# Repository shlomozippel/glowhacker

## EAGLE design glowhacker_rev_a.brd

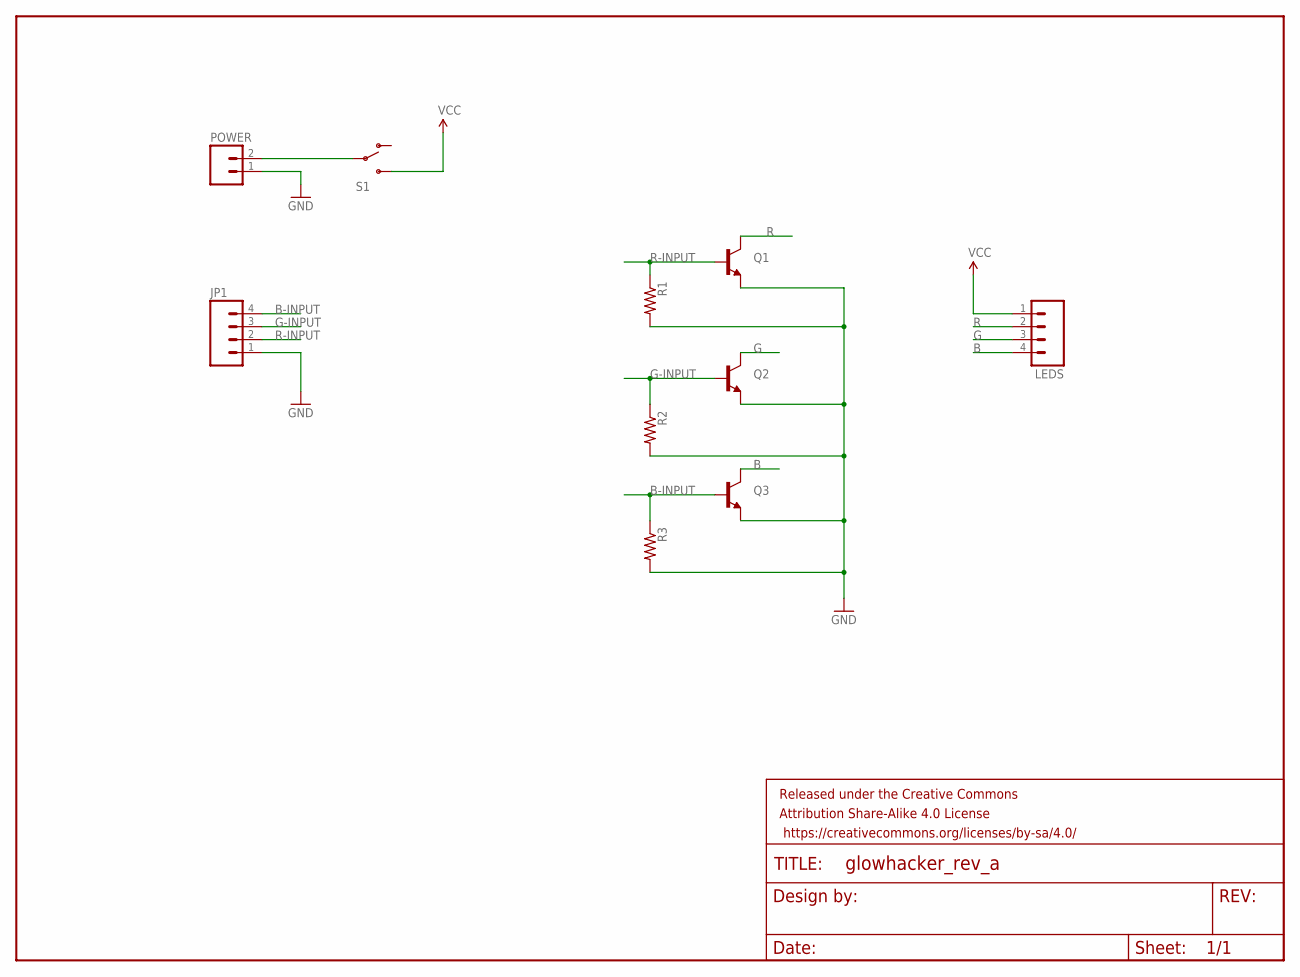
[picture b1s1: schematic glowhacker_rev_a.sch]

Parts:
FRAME1: FRAME-LETTER; CREATIVE_COMMONS
JP1: M04PTH; 1X04
LEDS: M04PTH; 1X04
POWER: M02PTH; 1X02
Q1, Q2, Q3: TRANSISTOR_NPNTO-92-AMMO; TO-92-AMMO
R1, R2, R3: RESISTOREZ; AXIAL-0.3EZ
S1: SWITCH-SPDTPTH; SWITCH-SPDT

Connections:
B: LEDS.4, Q3.3 (C)
B-INPUT: JP1.4, Q3.2 (B), R3.P$1 (1)
G: LEDS.3, Q2.3 (C)
G-INPUT: JP1.3, Q2.2 (B), R2.P$1 (1)
GND: JP1.1, POWER.1, Q1.1 (E), Q2.1 (E), Q3.1 (E), R1.P$2 (2), R2.P$2 (2), R3.P$2 (2)
unnamed: POWER.2, S1.2
R: LEDS.2, Q1.3 (C)
R-INPUT: JP1.2, Q1.2 (B), R1.P$1 (1)
VCC: LEDS.1, S1.3 (S)

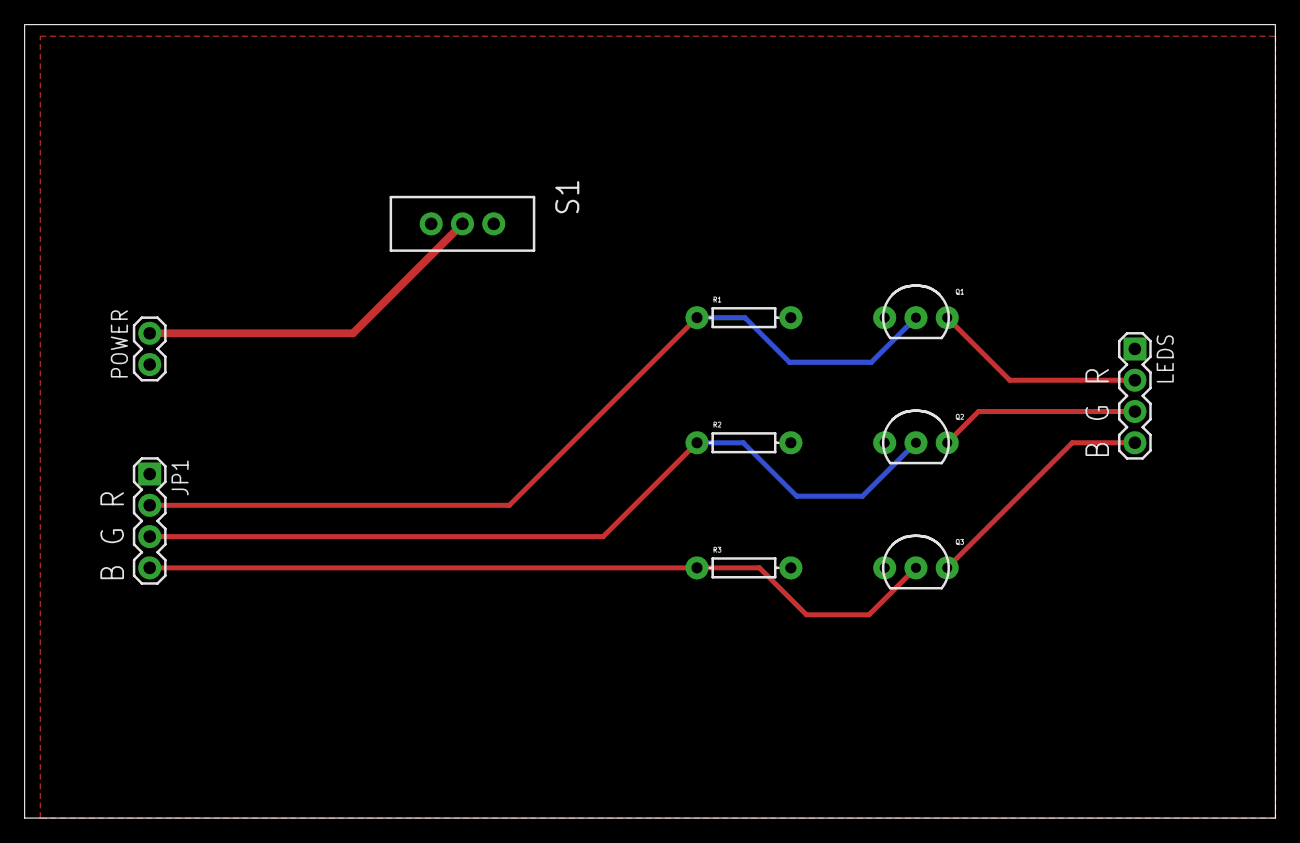
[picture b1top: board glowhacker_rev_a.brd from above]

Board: 2 copper layers, 101.6 x 64.4 mm, 11 parts (0 on the bottom side), 9 nets.

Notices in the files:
parts and their libraries:
SparkFun-Aesthetics: Licensing: Creative Commons ShareAlike 4.0 International - https://creativecommons.org/licenses/by-sa/4.0
SparkFun-Aesthetics: Released under the Creative Commons Attribution Share-Alike 4.0 License
SparkFun-Aesthetics: https://creativecommons.org/licenses/by-sa/4.0
